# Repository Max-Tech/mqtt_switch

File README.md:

# mqtt_switch
Arduino smart light switch, provide control smart home via MQTT broker

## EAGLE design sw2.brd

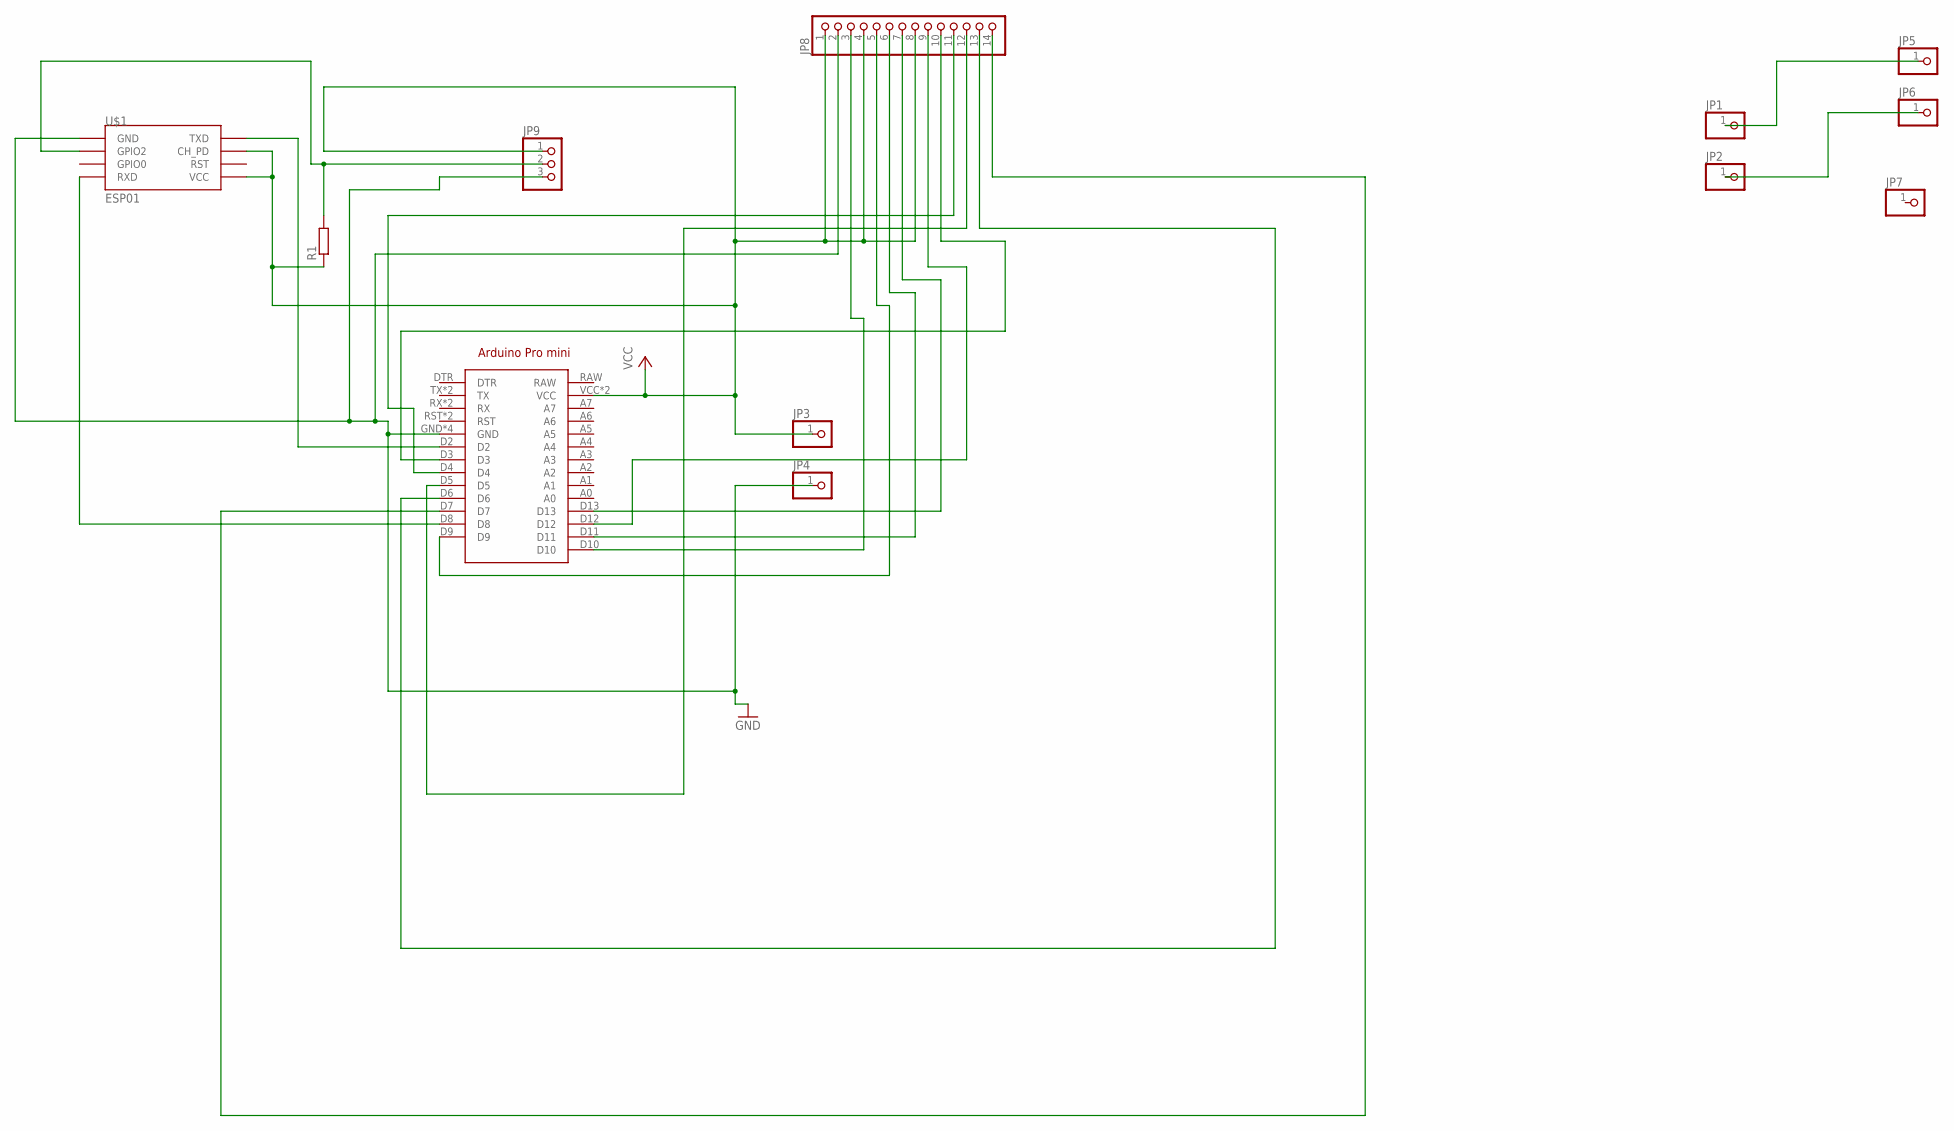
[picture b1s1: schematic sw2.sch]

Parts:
ARDUINO1: ARDUINO_PRO_MINI
JP1, JP2, JP3, JP4, JP5, JP6, JP7: PINHD-1X1; 1X01
JP8: PINHD-1X14-CB; 1X14-CB
JP9: PINHD-1X3; 1X03
R1: R-EU_0204/5; 0204/5
U$1: ESP01

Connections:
GND: ARDUINO1.GND, ARDUINO1.GND@1 (GND), ARDUINO1.GND@2 (GND), ARDUINO1.GND@3 (GND), JP4.1, JP8.2, JP9.3, U$1.GND
unnamed: JP1.1, JP5.1
unnamed: JP2.1, JP6.1
unnamed: ARDUINO1.D2, U$1.TX (TXD)
unnamed: ARDUINO1.D10, JP8.3
unnamed: JP9.2, R1.2, U$1.GPIO2
unnamed: ARDUINO1.D13, JP8.7
unnamed: ARDUINO1.D9, JP8.5
unnamed: ARDUINO1.D8, U$1.RX (RXD)
unnamed: ARDUINO1.D11, JP8.6
unnamed: ARDUINO1.D12, JP8.9
unnamed: ARDUINO1.D3, JP8.10
unnamed: ARDUINO1.D4, JP8.11
unnamed: ARDUINO1.D5, JP8.12
unnamed: ARDUINO1.D6, JP8.13
unnamed: ARDUINO1.D7, JP8.14
VCC: ARDUINO1.VCC, ARDUINO1.VCC@1 (VCC), JP3.1, JP8.1, JP8.4, JP8.8, JP9.1, R1.1, U$1.CH_PD, U$1.VCC

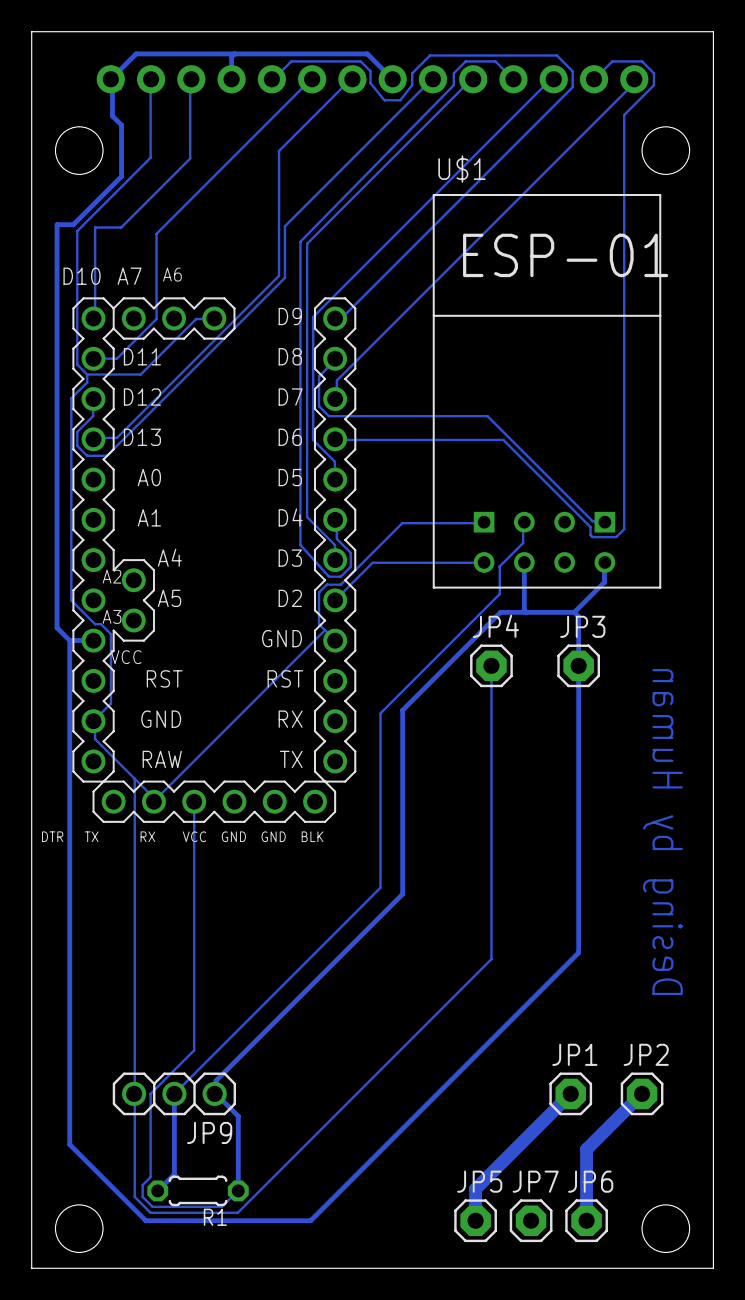
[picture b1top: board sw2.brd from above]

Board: 2 copper layers, 43.0 x 78.0 mm, 12 parts (0 on the bottom side), 17 nets.

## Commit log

2018-02-15 Create esp8266_mqtt
